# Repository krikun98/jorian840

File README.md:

# Jorian 840

44-key wireless split keyboard in a 100x100 mm PCB.

Two main versions are available with plenty of supported switches.

Plates and bottoms are to be cut from metal, acryllic or dual-layered plastic.

## Disclaimer

This is a modified version of Joric's Jorian.

The keyboard layout was derived from the [Jian layout](http://www.keyboard-layout-editor.com/#/gists/4b6c2af67148f58ddd6c6b2976c4370f) (just visually, there was no actual copying involved).
Please buy the Jian from its author, [/u/KgOfHedgehogs](http://reddit.com/u/KgOfHedgehogs) at [the official store](https://killswit.ch)

## Features

* Wireless via Holyiot 18010 modules
* Fully-featured ZMK split
* Uses either 233350 310 mAh, LIR2032 40 mAh or CR2032 220 mAh (non-rechargeable) batteries
* Charger on/off switch (for non-rechargeable batteries)
* Proper case support
* Adjustable pinky stagger in the solder version
* Can be built with 7 or 8 mm. standoffs even with the rechargeable battery under the PCB

## Download

You can download Gerber files and firmware in the [releases section](https://github.com/krikun98/jorian840/releases).
More images are also in Actions builds.

## Instructions

Please refer to the public [Jorian wiki](https://github.com/krikun98/jorian840/wiki).

For building the artifacts locally you need Docker. 
Just run the `build.sh` script.

However, everything is built in Actions. 
Check the Actions tab or releases for files not linked here.

### Firmware

The [bootloader](../../releases/latest/download/bootloader.hex) is available in the Releases tab.
Please refer to the [nrfmicro wiki](https://github.com/joric/nrfmicro/wiki/bootloader) for the flashing instructions.

[Default firmware](../../releases/latest/download/firmware.zip) files are also there, and you can use the [Jorian840](https://github.com/krikun98/zmk-config/tree/jorian840) `zmk-config` branch for customisation.

## Links

### Version 0.2

MX Hotswap 

[IBOM](https://htmlpreview.github.io/?https://github.com/krikun98/jorian840/blob/holyiot/pcb/hotswap/bom/ibom.html)

[gerbers](../../releases/latest/download/pcb_hotswap_gerbers.zip)

front|back
--|--
|

Solder (MX/Alps/Omron B3G-S)

[IBOM](https://htmlpreview.github.io/?https://github.com/krikun98/jorian840/blob/holyiot/pcb/solder/bom/ibom.html)

[gerbers](../../releases/latest/download/pcb_solder_gerbers.zip)

front|back
--|--
|

[Case files](../../releases/latest/download/case_files.zip) for all variations.

All the case files have the switch holes adjusted for laser cutting plastic (0.25 mm. smaller in both dimensions).
If your laser cutter has different tolerances - adjust them and re-run the build script.

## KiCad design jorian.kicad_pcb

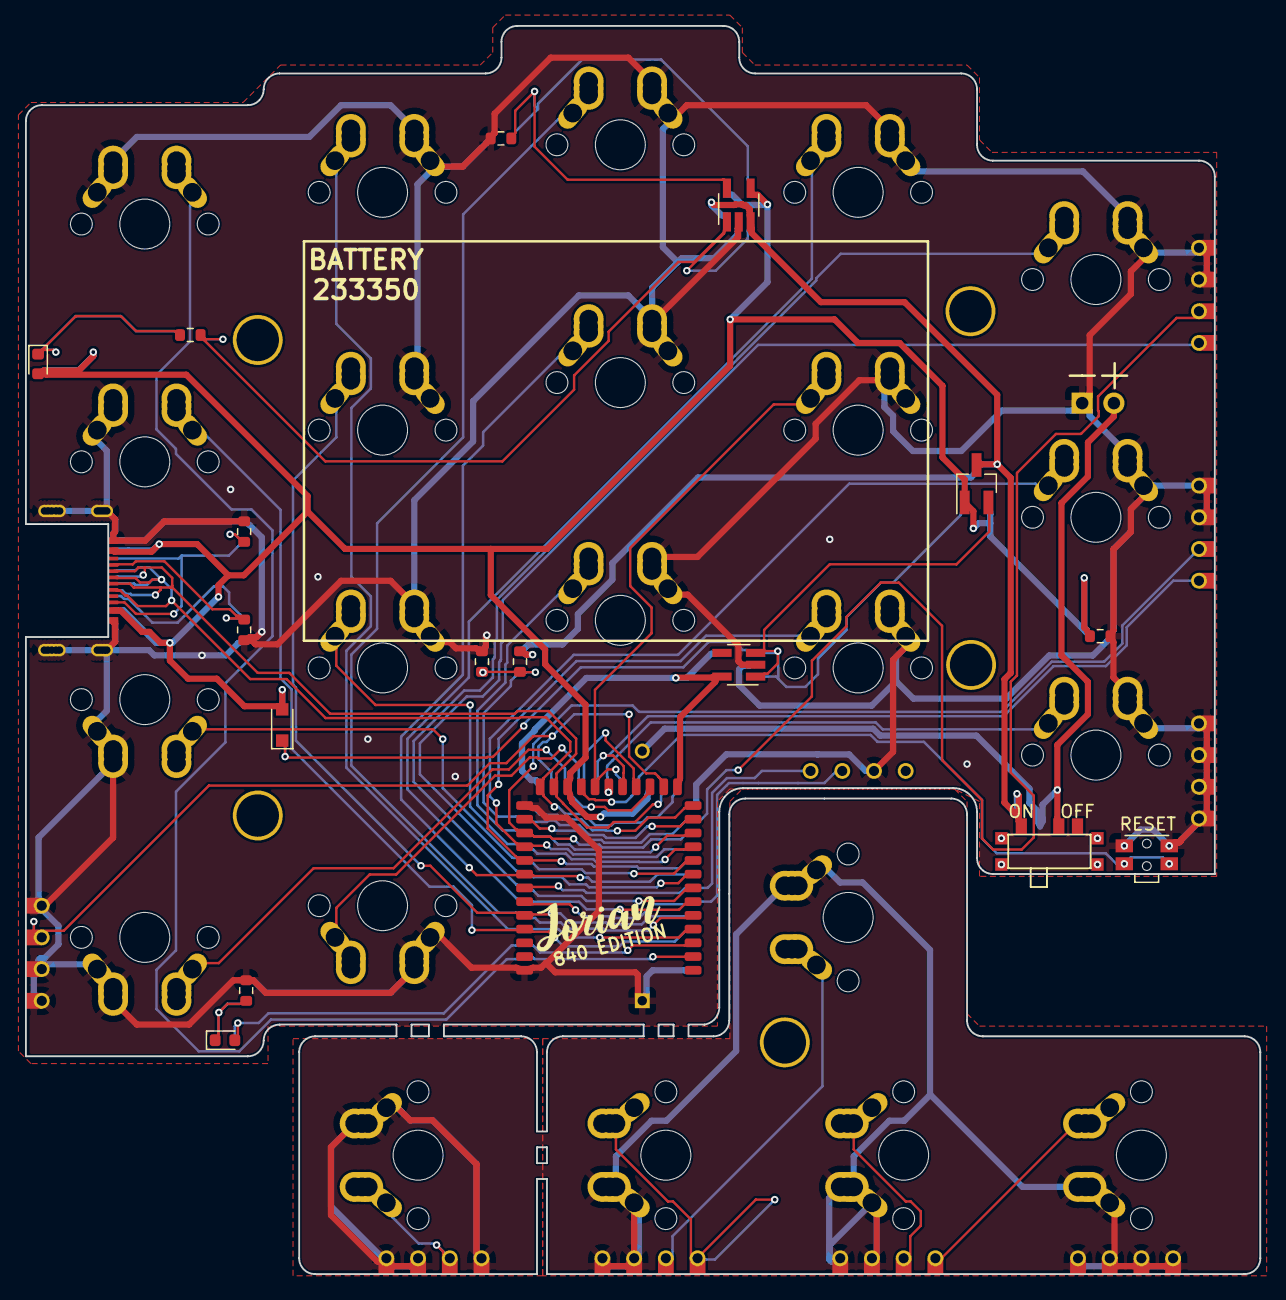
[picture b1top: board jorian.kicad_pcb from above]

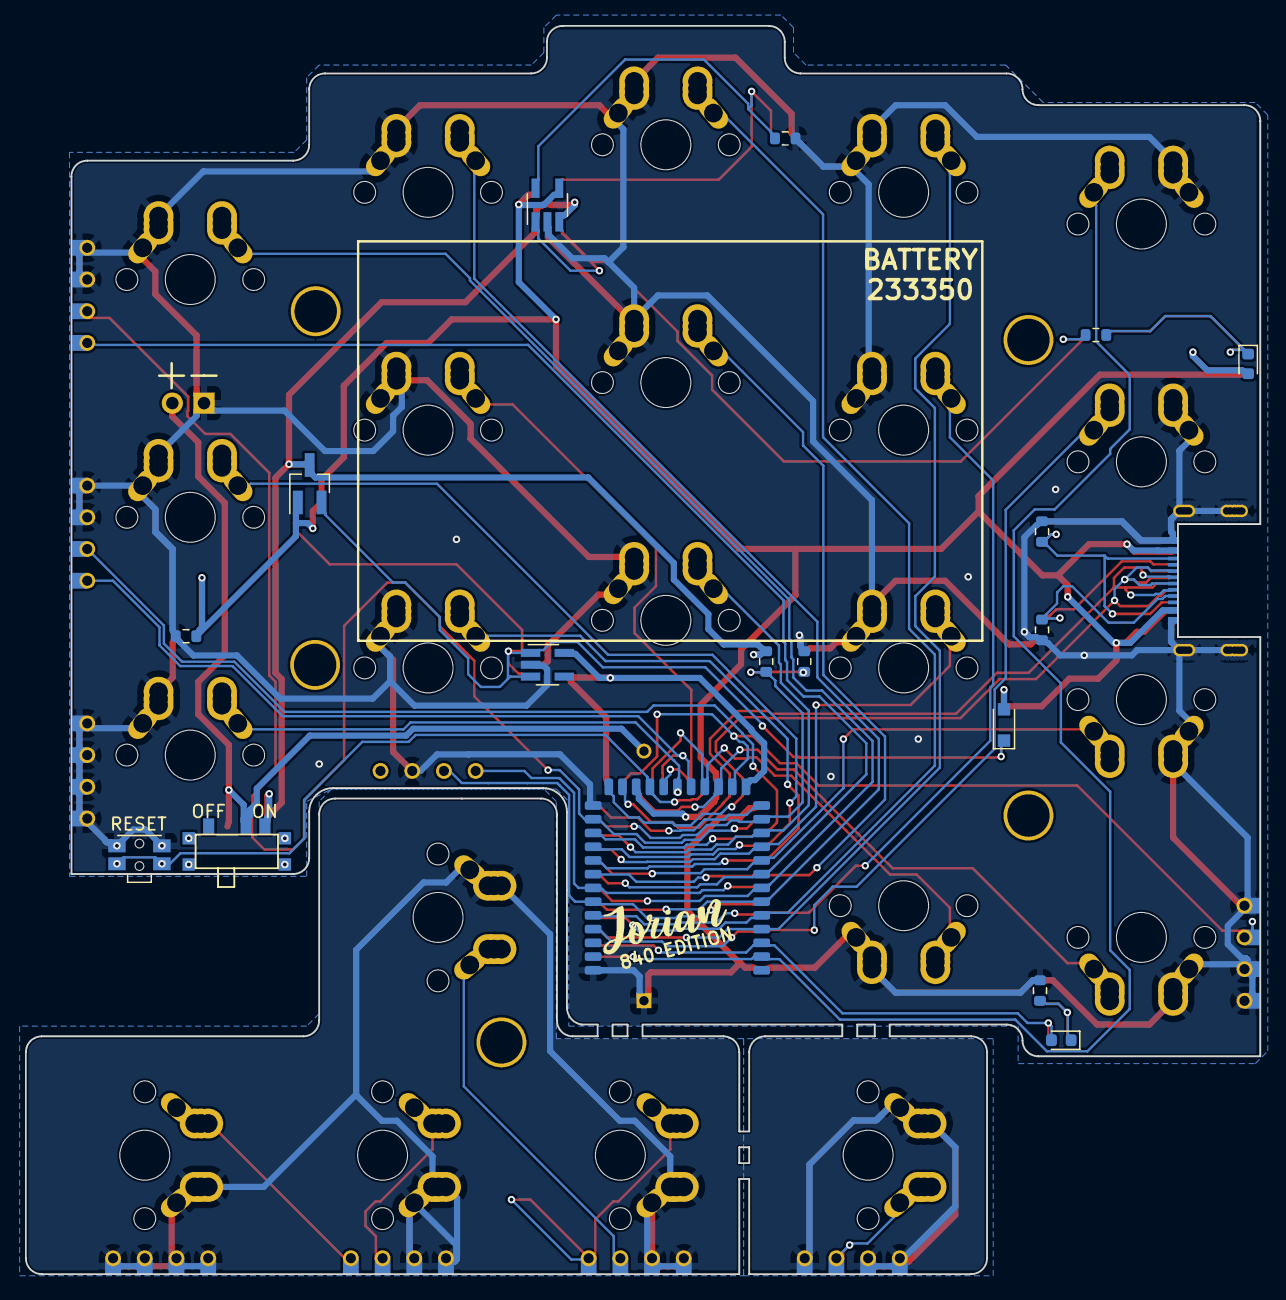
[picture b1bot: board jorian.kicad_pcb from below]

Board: 2 copper layers, 98.9 x 100.0 mm, 58 parts (5 on the bottom side), 48 nets.

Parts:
BT1: Battery Holder; cr2032_bs-7
D1: RED; LED_0603_1608Metric_REV
D2: 1N5819; D_SOD-323_HandSoldering_REV
D3: BLUE; LED_0603_1608Metric_REV
E5, E10, E15, E18: left; edge_conn
E16, E19, E20, E21: right; edge_conn
G1, G2: Logo_Open_Hardware_Small; jorian_logo
HM1, HM2, HM3, HM4, HM5: CaseHole; M2-MountingHole-Standoff
J1: USB-C Conn; USB-C_C168688_REV
J2: Ex_Bat; Battery_TH
JP16: SWD_conn; connector_swd
Q1: AO3407; SOT-23_Handsoldering_REV
R1, R2: 5.1K; R_0603_1608Metric_REV
R3, R8: 1K; R_0603_1608Metric_REV
R4: RPROG; R_0603_1608Metric_REV
R5: 820K; R_0603_1608Metric_REV
R6: 2M; R_0603_1608Metric_REV
R7: 100K; R_0603_1608Metric_REV
RSW1: SW_PUSH; SW_SPST_EVQP7C_REV
SW1, SW2, SW3, SW4, SW5, SW6, SW7, SW8, SW9, SW10, SW11, SW12, SW13, SW14, SW15, SW16, SW17, SW18, SW19, SW20, SW21, SW22: SW_PUSH; MX-Alps-1U-REV
SW23: SW_SPDT; SW_SPDT+H-MSK12C01_hor(7pin_SMD)_REV
U1: Holyiot-18010; Holyiot-18010-nRF52840-REV
U2: TP4054; SOT-23-5_HandSoldering_REV
U3: XC6220B331MR-G; SOT-23-5_HandSoldering_REV

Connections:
BATTERY_PIN: R5.2, R6.1, U1.12 (P0.04/AIN2)
BLUE_LED: D3.2 (A), U1.3 (P1.10)
CC1: J1.A5 (CC1), R2.1
CC2: J1.B5 (CC2), R1.1
DATA+: J1.A6 (D+), J1.B6 (D+), U1.24 (USB_D+)
DATA-: J1.A7 (D-), J1.B7 (D-), U1.23 (USB_D-)
GND: BT1.2 (-), E5.1, E5.2, E10.1, E10.2, E15.1, E15.2, E15.3, E15.4, E16.1, E16.3, E16.4, J1.A1 (GND), J1.S1 (SHIELD), J2.1, JP16.2, R1.2, R2.2, R4.2, R6.2, R7.2, R8.2, RSW1.2, SW1.1, SW2.2, SW3.2, SW4.2, SW5.2, SW6.1, SW7.2, SW8.2, SW9.2, SW10.2, SW11.2, SW12.2, SW13.2, SW14.2, SW15.2, SW16.2, SW17.1, U1.25 (GND), U1.37 (GND), U2.2 (VSS), U3.2 (GND)
GND_A: E18.1, E18.3, E18.4, SW18.2
GND_B: E19.1, E19.2, E20.1, E20.2, E21.1, E21.2, E21.3, E21.4, SW19.1, SW20.1, SW21.1, SW22.2
unnamed: D1.1 (K), R3.1
unnamed: D2.1 (K), Q1.2 (S), U3.1 (VIN), U3.3 (EN)
unnamed: D3.1 (K), R8.1
unnamed: R3.2, U2.1 (STAT)
unnamed: R4.1, U2.5 (PROG)
R1C1: E5.4, U1.8 (P0.28/AIN4)
R1C1B: E19.4, SW19.2
R1C2: SW5.1, U1.7 (P0.02/AIN0)
R1C3: SW4.1, U1.6 (P0.03/AIN1)
R1C4: SW3.1, U1.5 (P1.15)
R1C5: SW2.1, U1.4 (P1.13)
R1C6: SW1.2, U1.2 (P1.11)
R2C0: E5.3, U1.26 (P0.22)
R2C0B: E19.3, SW22.1
R2C1: E10.3, U1.27 (P1.00)
R2C1B: E20.3, SW20.2
R2C2: SW10.1, U1.28 (P1.03)
R2C3: SW9.1, U1.20 (P0.19)
R2C4: SW8.1, U1.30 (P1.02)
R2C5: SW7.1, U1.33 (P1.04)
R2C6: SW6.2, U1.34 (P1.06)
R3C1: E10.4, U1.18 (P0.23)
R3C1B: E20.4, SW21.2
R3C2: SW15.1, U1.19 (P0.21)
R3C3: SW14.1, U1.29 (P1.01)
R3C4: SW13.1, U1.11 (P0.31/AIN7)
R3C5: SW12.1, U1.10 (P0.30/AIN6)
R3C6: SW11.1, U1.9 (P0.29/AIN5)
R4C5: SW17.2, U1.17 (P0.12)
R4C6: SW16.1, U1.16 (P1.09)
R4C7: E16.2, U1.15 (P0.07)
R4C7A: E18.2, SW18.1
SWC: JP16.4, U1.31 (SWDCLK)
SWD: JP16.3, U1.32 (SWDIO)
VBAT: BT1.1 (+), J2.2, SW23.2 (B)
VBAT2: Q1.3 (D), R5.1, SW23.1 (A), U2.3 (VBAT)
VBUS: D1.2 (A), D2.2 (A), J1.A4 (VBUS), Q1.1 (G), R7.1, U1.22 (VBUS), U2.4 (VDD)
nRF_VDD: U1.14 (VDD), U3.5 (VOUT)
reset: RSW1.1, U1.21 (P0.18/RESET)

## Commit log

2021-12-11 Ready for 0.15 (6 mil) tolerances
2021-12-11 Hatch pattern, antenna keepout
2021-12-12 Adjusted tolerances, improved zone fills
2021-12-12 Added option to move pinky cluster
2021-12-12 Fixed power switch footprint
2021-12-12 Even more optimized routing
2021-12-12 Added pinky breakoff
2021-12-16 First fabbed revision
2021-12-16 Adjusted routing
2022-01-07 Jorian840 0.1
2022-01-07 Fixes
2022-01-07 Broken links
2022-01-07 Adjustments
2022-01-07 IBOM adjustments
2022-01-07 Maker's mark
2022-01-07 Features section
2022-01-07 IBOM maker's mark
2022-01-07 IBOM in readme
2022-01-07 Readme versioning
2022-01-07 Workflow draft
2022-01-07 Separate workflows further
2022-01-07 Forgot to save
2022-01-07 Execution permissions
2022-01-07 Typo
2022-01-07 Docker permission fix
2022-01-07 Order fix
2022-01-07 Artifacts
2022-01-07 Tabs
2022-01-07 Removed variable
2022-01-07 Readme updates from CI
2022-01-07 JQ magic
2022-01-07 Proper magic
2022-01-07 Proper magic fix
2022-01-07 Readme adjustment
2022-01-07 Generate images, DXF files and gerbers via Actions (#1)
    * Workflow draft
    * Separate workflows further
    * Forgot to save
    * Execution permissions
    * Typo
    * Docker permission fix
2022-01-07 Firmware links
2022-01-07 Hole note
2022-01-07 Download section adjustment
2022-01-07 Ignore readme updated for actions
2022-01-07 Feature mention
2022-01-07 CI edit
2022-01-08 Unnecessary files
2022-01-08 Proper library management
2022-01-08 Battery capacity fix
2022-01-11 Moved traces away from switches that would be cut down
2022-01-11 Updated case hole footprints
2022-01-11 Added top USB port version
2022-01-11 Library management update
2022-01-13 Work on bottom with AA holder
2022-01-13 Schematic ground fix
2022-05-31 fixed kikit version
2022-12-15 Added title image and video link
2023-10-11 Update actions
    Update version dependencies and formats
2023-10-11 Removed "untested" note from README
2023-10-11 KiKit 1.3.0 build script edits
